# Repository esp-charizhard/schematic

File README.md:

# schematic
The schematic and pcb layout for the charizhard project.

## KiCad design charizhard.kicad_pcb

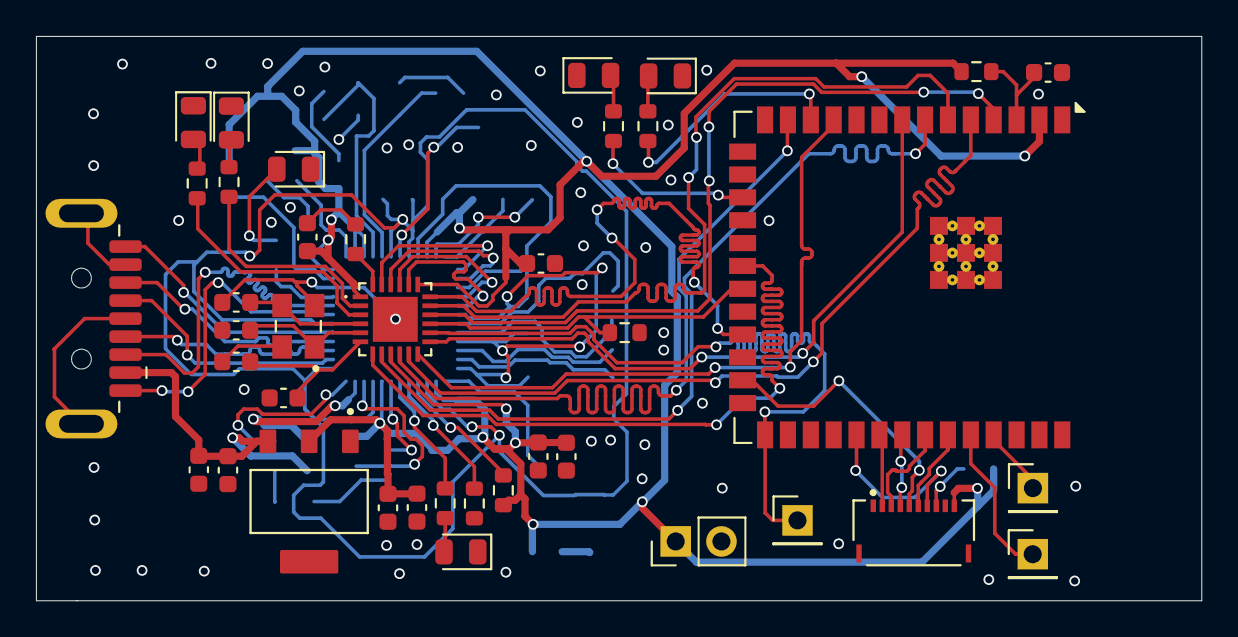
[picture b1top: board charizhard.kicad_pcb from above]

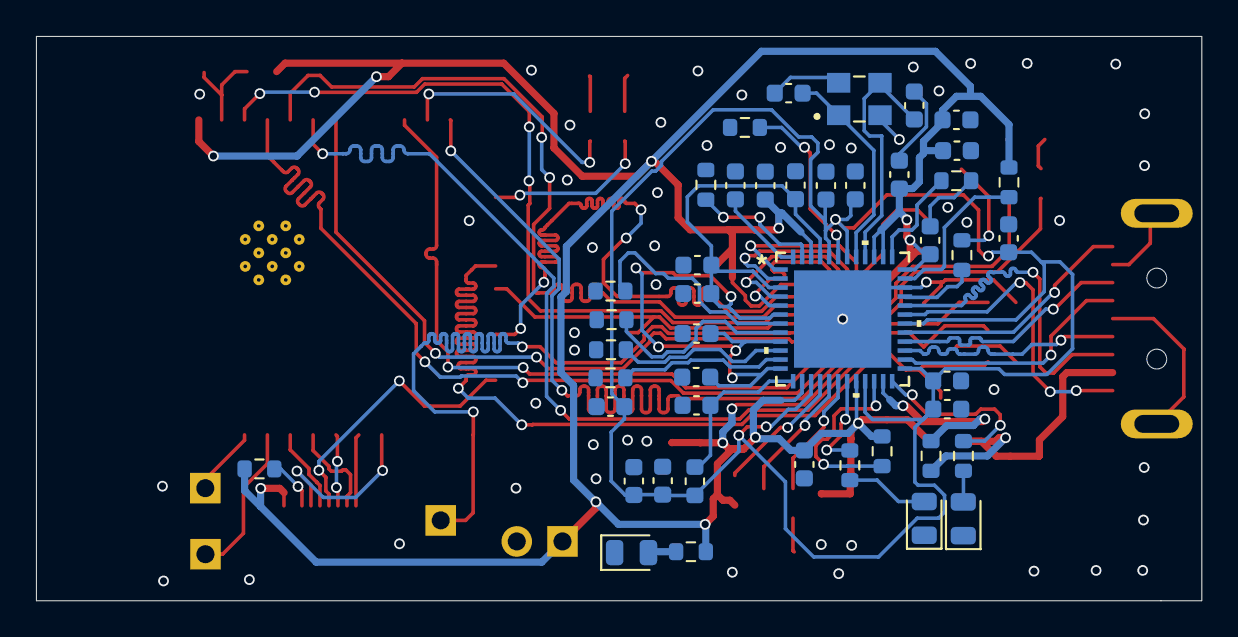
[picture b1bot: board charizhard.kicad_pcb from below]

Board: 2 copper layers, 64.7 x 31.4 mm, 83 parts (44 on the bottom side), 73 nets.

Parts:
C1, C3, C36: 22µF; C_0603_1608Metric
C2, C19, C26, C27, C29: 100nF; C_0603_1608Metric
C4, C5, C6, C7: 22pF; C_0603_1608Metric
C8, C11, C23, C25, C28: 1µF; C_0603_1608Metric
C9: 470pF; C_0603_1608Metric
C10: 1uF; C_0603_1608Metric
C12, C18: 10µF; C_0603_1608Metric
C13, C14, C15, C16, C17, C20, C21, C24, C30, C31, C32, C33, C34, C35, C37: 0.1µF; C_0603_1608Metric
D1, D3, D4, D5, D6, D8, D9, D10, D11: LED; D_0805_2012Metric
J1, J3, J11: Conn_01x01_Pin; PinHeader_1x01_P2.54mm_Vertical
J2: USB3_A Port USB; USB3_A_Plug_Wuerth_692112030100_Horizontal
J4: Conn_01x02_Pin; PinHeader_1x02_P2.54mm_Vertical
J5: Molex5034801000 - Connecteur pour le capteur digi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; MOLEX_5034801000
L1: 3.3µH; L_0603_1608Metric
R1, R3, R6, R8, R9, R12, R16, R18, R21, R24, R25, R27: 10KΩ; R_0603_1608Metric
R2, R4, R11, R17, R19, R20, R23: 330Ω; R_0603_1608Metric
R7: 12KΩ; R_0603_1608Metric
R10: 12.1KΩ; R_0603_1608Metric
R13, R14: 270Ω; R_0603_1608Metric
R15: 1KΩ; R_0603_1608Metric
R26: 2KΩ; R_0603_1608Metric
U1: ESP32-S3-WROOM-2 Micro-controleur; ESP32-S3-WROOM-2
U2: LAN7800-I/Y9X Controleur USB to Ethernet; 48SQFN-5304-7X7B_MCH
U4: LAN8720A-CP PHY pour la communication RMII; QFN50P400X400X100-25N
U5: AMS1117-3.3; SOT229P700X180-4N
Y1, Y3: ECS-250-18-33Q-DS; XTAL_ECS-250-18-33Q-DS

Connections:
/3.3V: C2.1, C3.1, C26.2, C27.2, C28.2, C29.2, C32.1, C33.1, C34.1, C35.2, C36.2, C37.2, J4.1, J5.10, R1.1, R4.1, R6.1, R8.1, R12.1, R27.1, U1.2 (3V3), U2.14 (VDD_SW_IN), U2.20 (VDDVARIO), U2.36 (VDDVARIO), U2.38 (VDD33A), U2.39 (VDDVARIO), U2.46 (VDD33_REG_IN), U4.1 (VDD2A), U4.9 (VDDIO), U4.19 (VDD1A), U5.2 (VOUT)
GND: C1.2, C2.2, C3.2, C4.2, C5.1, C6.2, C7.1, C8.2, C9.2, C10.1, C11.2, C12.2, C13.2, C14.2, C15.2, C16.2, C17.1, C18.2, C19.2, C20.2, C21.2, C23.2, C24.2, C25.1, C26.1, C27.1, C28.1, C29.1, C30.2, C31.2, C32.2, C33.2, C34.2, C35.1, C36.1, C37.1, D1.1 (K), D3.1 (K), D4.1 (K), D5.1 (K), D6.1 (K), D8.1 (K), D9.1 (K), D10.1 (K), D11.1 (K), J2.4 (GND), J2.7 (DRAIN), J2.10 (SHIELD), J4.2, J5.1, J5.S1 (SHIELD), J5.S2 (SHIELD), R3.2, R7.2, R9.1, R10.2, R16.1, R18.1, R21.1, R24.1, R25.1, R26.1, U1.1 (GND), U1.16 (IO46), U1.26 (IO45), U1.40 (GND), U1.41 (GND), U2.34 (TEST), U2.49 (VSS), U4.25 (VSS), U5.1 (GND/ADJ), Y1.2 (GND), Y1.4 (GND), Y3.2 (GND), Y3.4 (GND)
unnamed: D1.2 (A), R4.2
unnamed: D3.2 (A), R17.1
unnamed: D4.2 (A), R19.2
unnamed: D5.2 (A), R20.2
unnamed: D6.2 (A), R23.1
unnamed: D8.2 (A), R2.2
unnamed: D9.2 (A), R11.2
unnamed: D10.2 (A), R13.2
unnamed: D11.2 (A), R14.2
unnamed: J1.1, U1.37 (TXD0/IO43)
unnamed: J2.3 (D+), U2.26 (USB2_DP)
unnamed: J2.2 (D-), U2.27 (USB2_DM)
unnamed: J2.6 (SSRX+), U2.28 (USB3_TXDP)
unnamed: J2.5 (SSRX-), U2.29 (USB3_TXDM)
unnamed: J2.9 (SSTX+), U2.31 (USB3_RXDP)
unnamed: J2.8 (SSTX-), U2.32 (USB3_RXDM)
unnamed: C1.1, C19.1, J2.1 (VBUS), R15.1, U5.3 (VIN)
unnamed: J3.1, U1.36 (RXD0/IO44)
unnamed: J5.8, R1.2
unnamed: J11.1, U1.27 (IO0), U4.14 (~NINT/REFCLKO)
unnamed: C25.2, R12.2, U1.3 (EN)
unnamed: U1.4 (IO4), U4.16 (TXEN)
unnamed: U1.5 (IO5), U4.11 (CRS_DV/MODE2)
unnamed: U1.6 (IO6), U4.17 (TXD0)
unnamed: U1.7 (IO7), U4.8 (RXD0/MODE0)
unnamed: R2.1, U1.12 (IO8)
unnamed: R11.1, U1.17 (IO9)
unnamed: U1.20 (IO12), U4.7 (RXD1/MODE1)
unnamed: R3.1, U1.21 (IO13), U4.15 (~NRST)
unnamed: U1.8 (IO15), U4.13 (MDC)
unnamed: U1.11 (IO18), U4.12 (MDIO)
unnamed: U1.23 (IO21), U4.18 (TXD1)
unnamed: J5.7, U1.31 (IO38)
unnamed: J5.5, U1.25 (IO48)
unnamed: J5.2, U1.32 (MTCK/IO39)
unnamed: J5.3, U1.34 (MTDI/IO41)
unnamed: J5.4, U1.33 (MTDO/IO40)
unnamed: J5.6, U1.35 (MTMS/IO42)
unnamed: U1.13 (USB_D-/IO19), U4.10 (RXER/PHYADO)
unnamed: R23.2, U2.19 (EECLK/LED1/GPIO3)
unnamed: R27.2, U2.16 (EECS/GPIO0)
unnamed: R21.2, U2.17 (EEDI/GPIO1)
unnamed: R20.1, U2.18 (EEDO/LED0/GPIO2)
unnamed: R19.1, U2.33 (LED3/GPIO6)
unnamed: R9.2, U2.43 (PME_MODE/GPIO7)
unnamed: R6.2, U2.22 (PME_N/GPIO4)
unnamed: C10.2, U2.48 (REF_FILT)
unnamed: R26.2, U2.47 (REF_REXT)
unnamed: R8.2, U2.35 (RESET_N/PME_CLEAR)
unnamed: R17.2, U2.24 (SUSPEND_N/LED2/GPIO5)
unnamed: U2.2 (TR0N), U4.22 (RXN)
unnamed: U2.1 (TR0P), U4.23 (RXP)
unnamed: U2.5 (TR1N), U4.20 (TXN)
unnamed: U2.4 (TR1P), U4.21 (TXP)
unnamed: R25.2, U2.8 (TR2N)
unnamed: R24.2, U2.7 (TR2P)
unnamed: R18.2, U2.11 (TR3N)
unnamed: R16.2, U2.10 (TR3P)
unnamed: R7.1, U2.37 (USBRBIAS)
unnamed: R15.2, U2.23 (VBUS_DET)
unnamed: C12.1, L1.2, U2.13 (VDD12_SW_OUT)
unnamed: C20.1, C23.1, C24.1, C30.1, C31.1, U2.3 (VDD25A), U2.6 (VDD25A), U2.9 (VDD25A), U2.12 (VDD25A), U2.45 (VDD25_REG_OUT)
unnamed: C7.2, U2.40 (XI), Y1.3 (OUT/IN)
unnamed: C6.1, U2.41 (XO), Y1.1 (IN/OUT)
unnamed: C11.1, C13.1, C14.1, C15.1, C16.1, C17.2, C18.1, C21.1, L1.1, U2.15 (VDD12_SW_FB), U2.21 (VDD12CORE), U2.25 (VDD12A), U2.30 (VDD12A), U2.42 (VDD12CORE), U2.44 (VDD12A)
unnamed: R13.1, U4.3 (LED1/REGOFF)
unnamed: R14.1, U4.2 (LED2/~NINTSEL)
unnamed: R10.1, U4.24 (RBIAS)
unnamed: C8.1, C9.1, U4.6 (VDDCR)
unnamed: C5.2, U4.5 (XTAL1/CLKLN), Y3.1 (IN/OUT)
unnamed: C4.1, U4.4 (XTAL2), Y3.3 (OUT/IN)

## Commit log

2025-05-24 init commit
2025-05-24 remove useless files
2025-05-24 swap DI/DO on eeprom
2025-05-25 fix data lines noise+impedance
2025-05-25 add dc blocking caps on usb3 data line
2025-05-27 remove useless res
2025-05-27 fixes?
